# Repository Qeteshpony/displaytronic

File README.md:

# Displaytronic VS2812 Driver Board

Replacement driver board and firmware for the Displaytronic VS2812 flipdot display (28×12 dots).

> **Status:** Work in progress – hardware not yet built or tested.

## Contents

| Path | Description |
|---|---|
| [`pcb/`](pcb/) | KiCad project of the driver board – see [Hardware Documentation](https://qeteshpony.github.io/displaytronic) |
| [`firmware/`](firmware/) | ATmega328P firmware (PlatformIO) – see [firmware README](firmware/README.md) |
| [`flipdot board/`](flipdot%20board/) | Reverse engineered schematics of the display itself |

Prebuilt firmware and production files are attached to each [release](https://github.com/Qeteshpony/displaytronic/releases). Changes are listed in the [changelog](CHANGELOG.md).

## License

- Hardware: [CERN-OHL-P-2.0](LICENSE-CERN-OHL-P-2.0)
- Firmware: [BSD-2-Clause](LICENSE-BSD-2-Clause)

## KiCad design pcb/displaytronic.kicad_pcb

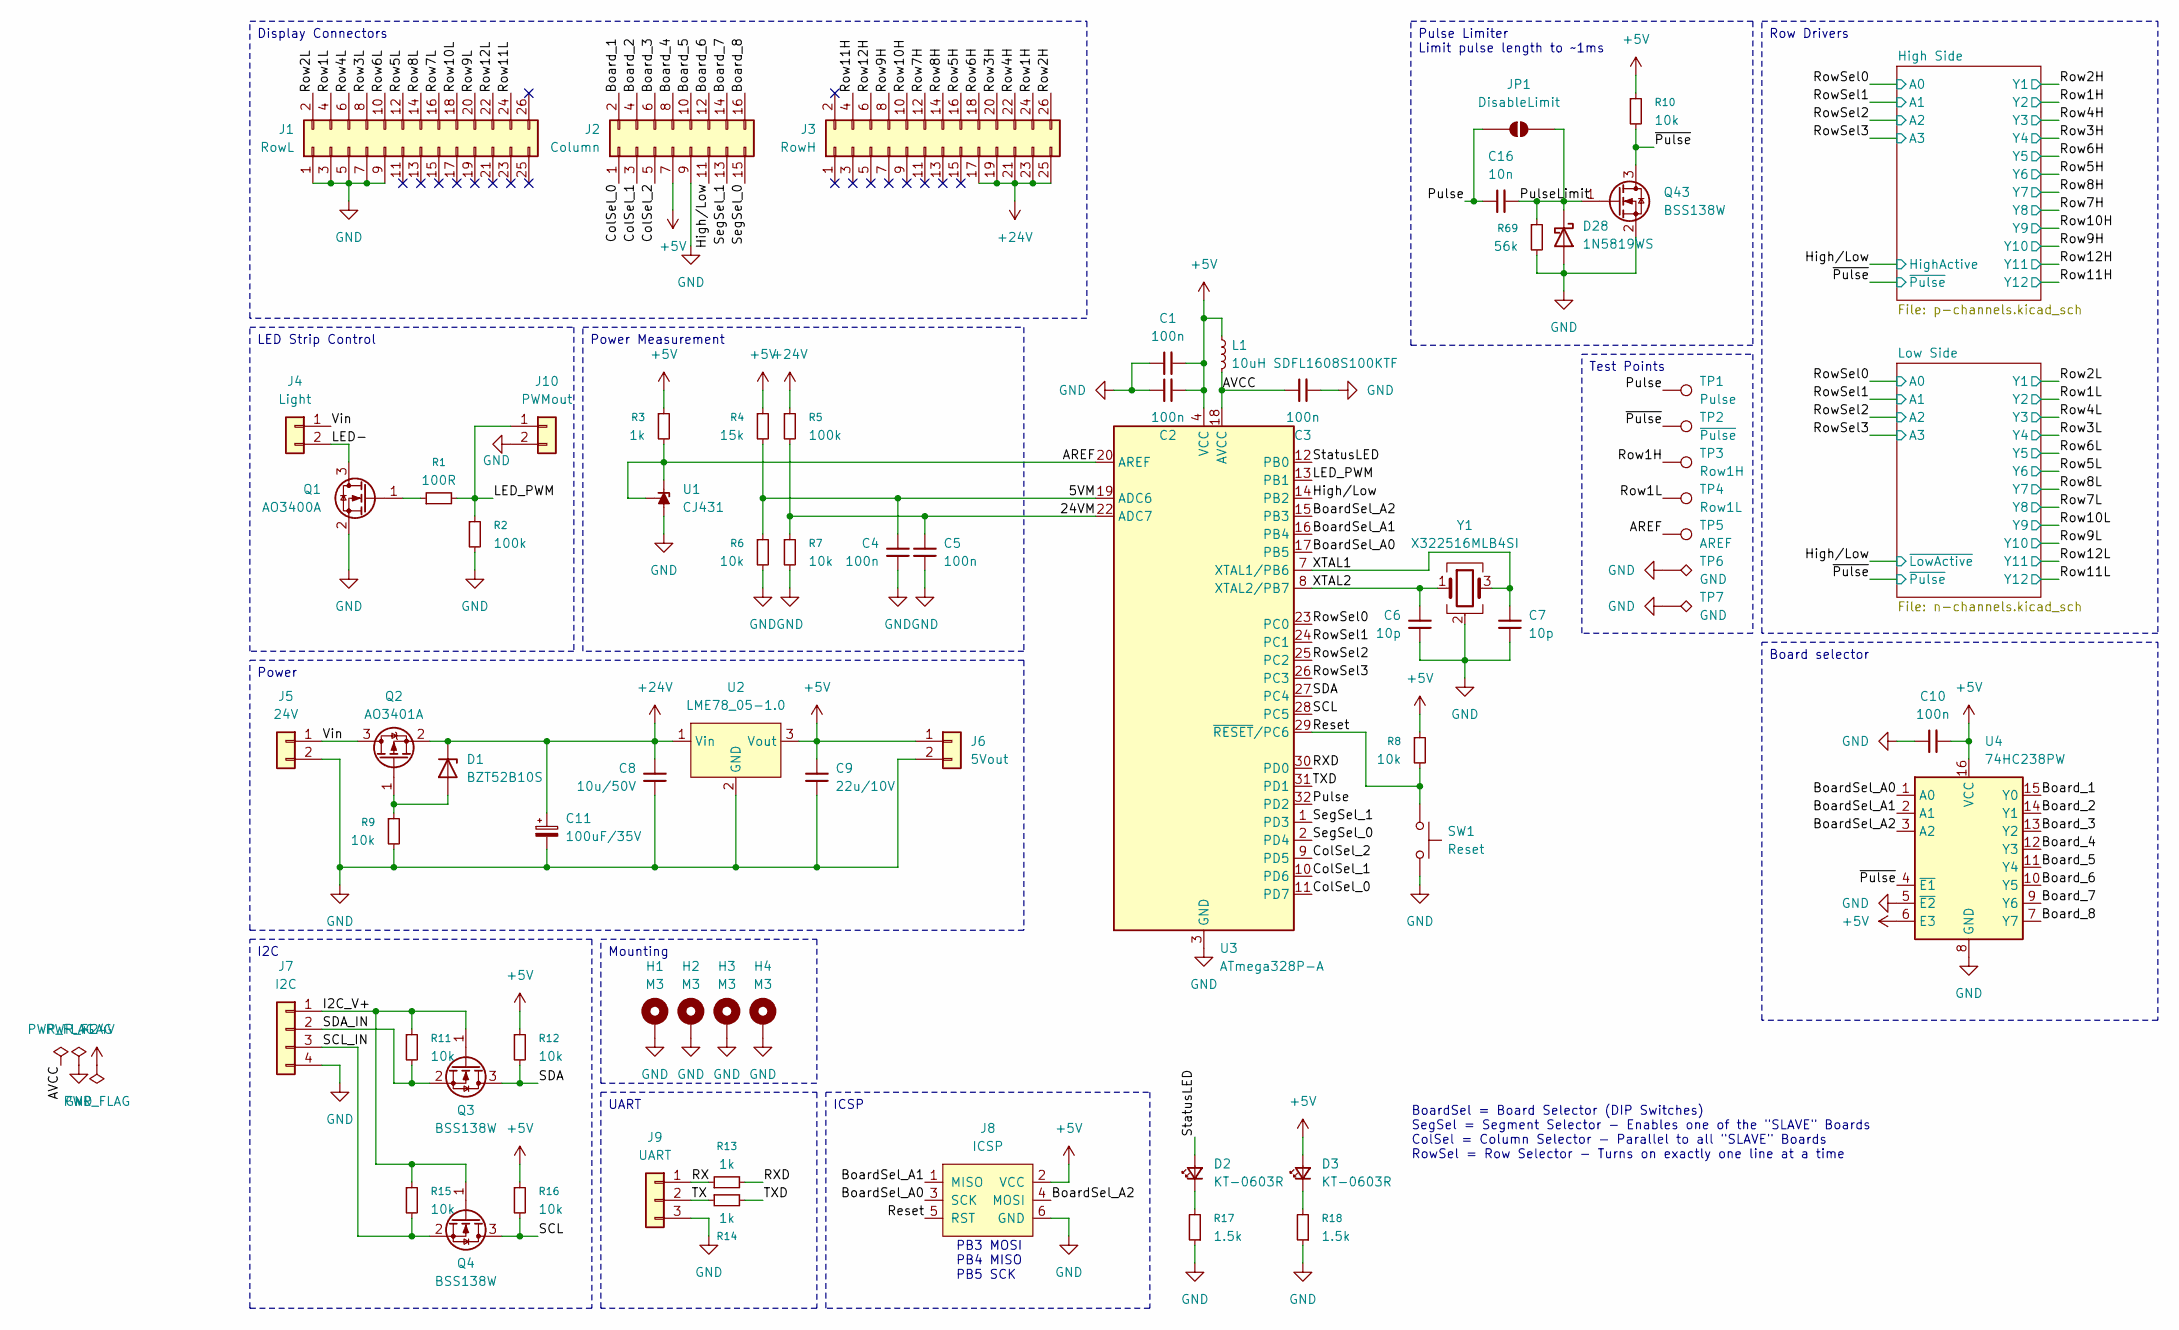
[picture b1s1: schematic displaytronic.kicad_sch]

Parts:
C1, C2, C3, C4, C5, C10: 100n; C_0402_1005Metric; LCSC C307331
C6, C7: 10p; C_0402_1005Metric; LCSC C32949
C8: 10u/50V; C_1206_3216Metric; LCSC C13585
C9: 22u/10V; C_1206_3216Metric; LCSC C12891
C11: 100uF/35V; CP_Radial_D8.0mm_P3.50mm
C16: 10n; C_0402_1005Metric; LCSC C15195
D1: BZT52B10S; D_SOD-323; LCSC C22399886
D2, D3: KT-0603R; LED_0603_1608Metric; LCSC C2286
D28: 1N5819WS; D_SOD-323; LCSC C191023
H1, H2, H3, H4: M3; MountingHole_3.2mm_M3_Pad
J1: RowL; IDC-Header_2x13_P2.54mm_Vertical
J2: Column; IDC-Header_2x08_P2.54mm_Vertical
J3: RowH; IDC-Header_2x13_P2.54mm_Vertical
J4: Light; CTB9352-2
J5: 24V; CTB9352-2
J6: 5Vout; JST_PH_B2B-PH-K_1x02_P2.00mm_Vertical
J7: I2C; JST_PH_B4B-PH-K_1x04_P2.00mm_Vertical
J8: ICSP; PinHeader_2x03_P2.54mm_Vertical
J9: UART; JST_PH_B3B-PH-K_1x03_P2.00mm_Vertical
J10: PWMout; JST_PH_B2B-PH-K_1x02_P2.00mm_Vertical
JP1: DisableLimit; SolderJumper-2_P1.3mm_Open_RoundedPad1.0x1.5mm
L1: 10uH SDFL1608S100KTF; L_0603_1608Metric; LCSC C1035
Q1: AO3400A; SOT-23; LCSC C20917
Q2: AO3401A; SOT-23; LCSC C15127
Q3, Q4, Q43: BSS138W; SOT-323_SC-70; LCSC C28646265
R1: 100R; R_0402_1005Metric; LCSC C25076
R2, R5: 100k; R_0402_1005Metric; LCSC C25741
R3, R13, R14: 1k; R_0402_1005Metric; LCSC C11702
R4: 15k; R_0402_1005Metric; LCSC C25756
R6, R7, R8, R9, R10, R11, R12, R15, R16: 10k; R_0402_1005Metric; LCSC C25744
R17, R18: 1.5k; R_0402_1005Metric; LCSC C25867
R69: 56k; R_0402_1005Metric; LCSC C25796
SW1: Reset; SW_Push_SPST_NO_Alps_SKRK; LCSC C720477
TP1: Pulse; TestPoint_Pad_D2.0mm
TP2: ~{Pulse}; TestPoint_Pad_D2.0mm
TP3: Row1H; TestPoint_Pad_D2.0mm
TP4: Row1L; TestPoint_Pad_D2.0mm
TP5: AREF; TestPoint_Pad_D2.0mm
TP6, TP7: GND; TestPoint_Pad_2.0x2.0mm
U1: CJ431; SOT-23; LCSC C3113
U2: LME78_05-1.0; LME78_1.0-Series
U3: ATmega328P-A; TQFP-32_7x7mm_P0.8mm; LCSC C14877
U4: 74HC238PW; TSSOP-16_4.4x5mm_P0.65mm; LCSC C60434
Y1: X322516MLB4SI; Crystal_SMD_3225-4Pin_3.2x2.5mm; LCSC C13738

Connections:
+5V: C1.2, C2.2, C9.2, C10.2, D3.2 (A), J2.7, J6.1, J8.2 (VCC), L1.1, R3.1, R4.1, R8.1, R10.1, R12.1, R16.1, U2.3 (Vout), U3.4 (VCC), U3.6 (VCC), U4.6 (E3), U4.16 (VCC); also elsewhere on the board
+24V: C8.2, C11.1, D1.1 (K), J3.17, J3.19, J3.21, J3.23, J3.25, Q2.2 (S), R5.1, U2.1 (Vin); also elsewhere on the board
/5VM: C4.2, R4.2, R6.1, U3.19 (ADC6)
/24VM: C5.2, R5.2, R7.1, U3.22 (ADC7)
/AREF: R3.2, TP5.1 (1_1), U1.1 (K), U1.2 (REF), U3.20 (AREF)
/AVCC: C3.2, L1.2, U3.18 (AVCC)
/BoardSel_A0: J8.3 (SCK), U3.17 (PB5), U4.1 (A0)
/BoardSel_A1: J8.1 (MISO), U3.16 (PB4), U4.2 (A1)
/BoardSel_A2: J8.4 (MOSI), U3.15 (PB3), U4.3 (A2)
/Board_1: J2.2, U4.15 (Y0)
/Board_2: J2.4, U4.14 (Y1)
/Board_3: J2.6, U4.13 (Y2)
/Board_4: J2.8, U4.12 (Y3)
/Board_5: J2.10, U4.11 (Y4)
/Board_6: J2.12, U4.10 (Y5)
/Board_7: J2.14, U4.9 (Y6)
/Board_8: J2.16, U4.7 (Y7)
/ColSel_0: J2.1, U3.11 (PD7)
/ColSel_1: J2.3, U3.10 (PD6)
/ColSel_2: J2.5, U3.9 (PD5)
/High/Low: J2.11, U3.14 (PB2); also elsewhere on the board
/I2C_V+: J7.1, Q3.1 (G), Q4.1 (G), R11.1, R15.1
/LED-: J4.2, Q1.3 (D)
/LED_PWM: J10.1, R1.2, R2.1, U3.13 (PB1)
/Pulse: C16.2, JP1.1 (A), TP1.1 (1_1), U3.32 (PD2)
/PulseLimit: C16.1, D28.1 (K), JP1.2 (B), Q43.1 (G), R69.1
/RX: J9.1, R13.1
/RXD: R13.2, U3.30 (PD0)
/Reset: J8.5 (RST), R8.2, SW1.1, U3.29 (~RESET/PC6)
/Row1H: J3.24, TP3.1 (1_1); also elsewhere on the board
/Row1L: J1.4, TP4.1 (1_1); also elsewhere on the board
/Row2H: J3.26; also elsewhere on the board
/Row2L: J1.2; also elsewhere on the board
/Row3H: J3.20; also elsewhere on the board
/Row3L: J1.8; also elsewhere on the board
/Row4H: J3.22; also elsewhere on the board
/Row4L: J1.6; also elsewhere on the board
/Row5H: J3.16; also elsewhere on the board
/Row5L: J1.12; also elsewhere on the board
/Row6H: J3.18; also elsewhere on the board
/Row6L: J1.10; also elsewhere on the board
/Row7H: J3.12; also elsewhere on the board
/Row7L: J1.16; also elsewhere on the board
/Row8H: J3.14; also elsewhere on the board
/Row8L: J1.14; also elsewhere on the board
/Row9H: J3.8; also elsewhere on the board
/Row9L: J1.20; also elsewhere on the board
/Row10H: J3.10; also elsewhere on the board
/Row10L: J1.18; also elsewhere on the board
/Row11H: J3.4; also elsewhere on the board
/Row11L: J1.24; also elsewhere on the board
/Row12H: J3.6; also elsewhere on the board
/Row12L: J1.22; also elsewhere on the board
/RowSel0: U3.23 (PC0); also elsewhere on the board
/RowSel1: U3.24 (PC1); also elsewhere on the board
/RowSel2: U3.25 (PC2); also elsewhere on the board
/RowSel3: U3.26 (PC3); also elsewhere on the board
/SCL: Q4.3 (D), R16.2, U3.28 (PC5)
/SCL_IN: J7.3, Q4.2 (S), R15.2
/SDA: Q3.3 (D), R12.2, U3.27 (PC4)
/SDA_IN: J7.2, Q3.2 (S), R11.2
/SegSel_0: J2.15, U3.2 (PD4)
/SegSel_1: J2.13, U3.1 (PD3)
/StatusLED: D2.2 (A), U3.12 (PB0)
/TX: J9.2, R14.1
/TXD: R14.2, U3.31 (PD1)
/Vin: J4.1, J5.1, Q2.3 (D)
/XTAL1: C7.2, U3.7 (XTAL1/PB6), Y1.3
/XTAL2: C6.2, U3.8 (XTAL2/PB7), Y1.1
/~Pulse: Q43.3 (D), R10.2, TP2.1 (1_1), U4.4 (~E1); also elsewhere on the board
GND: C1.1, C2.1, C3.1, C4.1, C5.1, C6.1, C7.1, C8.1, C9.1, C10.1, C11.2, D28.2 (A), H1.1 (1_1), H2.1 (1_1), H3.1 (1_1), H4.1 (1_1), J1.1, J1.3, J1.5, J1.7, J1.9, J2.9, J5.2, J6.2, J7.4, J8.6 (GND), J9.3, J10.2, Q1.2 (S), Q43.2 (S), R2.2, R6.2, R7.2, R9.2, R17.1, R18.1, R69.2, SW1.2, TP6.1 (1_1), TP7.1 (1_1), U1.3 (A), U2.2 (GND), U3.3 (GND), U3.5 (GND), U3.21 (GND), U4.5 (~E2), U4.8 (GND), Y1.2 (G), Y1.4 (G); also elsewhere on the board
unnamed: D1.2 (A), Q2.1 (G), R9.1
unnamed: D2.1 (K), R17.2
unnamed: D3.1 (K), R18.2
unnamed: Q1.1 (G), R1.1

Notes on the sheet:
PB3 MOSI PB4 MISO PB5 SCK
BoardSel = Board Selector (DIP Switches) SegSel = Segment Selector - Enables one of the "SLAVE" Boards ColSel = Column Selector - Parallel to all "SLAVE" Boards RowSel = Row Selector - Turns on exactly one line at a time
Mounting
Board selector
ICSP
UART
Power Measurement
LED Strip Control
I2C
Pulse Limiter Limit pulse length to ~1ms
Row Drivers
Power
Test Points
Display Connectors

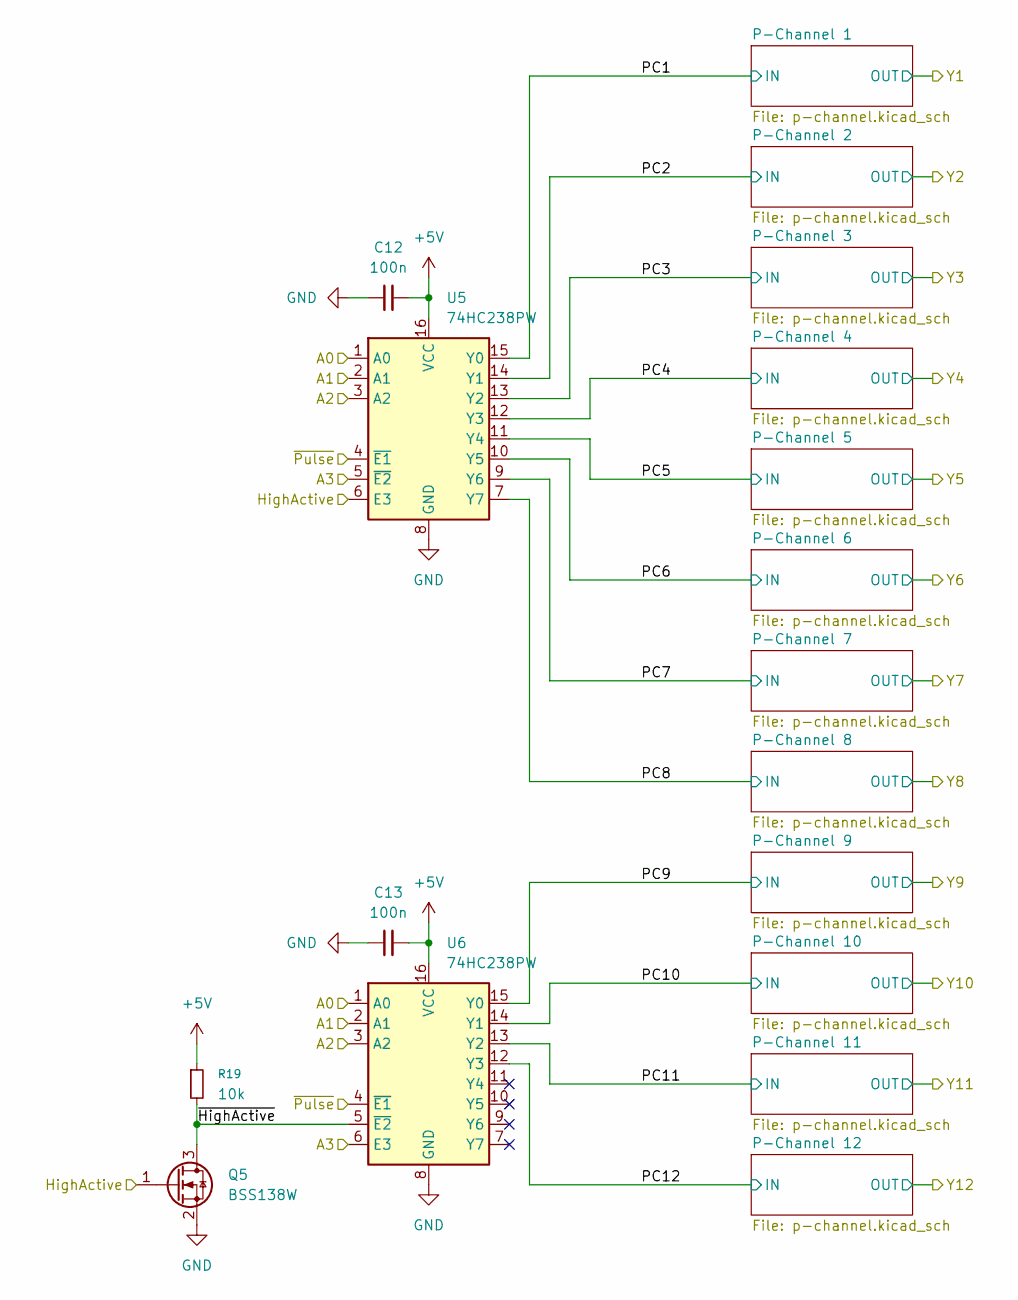
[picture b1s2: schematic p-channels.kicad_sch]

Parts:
C12, C13: 100n; C_0402_1005Metric; LCSC C307331
Q5: BSS138W; SOT-323_SC-70; LCSC C28646265
R19: 10k; R_0402_1005Metric; LCSC C25744
U5, U6: 74HC238PW; TSSOP-16_4.4x5mm_P0.65mm; LCSC C60434

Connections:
+5V: C12.2, C13.2, R19.1, U5.16 (VCC), U6.16 (VCC); also elsewhere on the board
/High Side/PC1: U5.15 (Y0); also elsewhere on the board
/High Side/PC2: U5.14 (Y1); also elsewhere on the board
/High Side/PC3: U5.13 (Y2); also elsewhere on the board
/High Side/PC4: U5.12 (Y3); also elsewhere on the board
/High Side/PC5: U5.11 (Y4); also elsewhere on the board
/High Side/PC6: U5.10 (Y5); also elsewhere on the board
/High Side/PC7: U5.9 (Y6); also elsewhere on the board
/High Side/PC8: U5.7 (Y7); also elsewhere on the board
/High Side/PC9: U6.15 (Y0); also elsewhere on the board
/High Side/PC10: U6.14 (Y1); also elsewhere on the board
/High Side/PC11: U6.13 (Y2); also elsewhere on the board
/High Side/PC12: U6.12 (Y3); also elsewhere on the board
/High Side/~HighActive: Q5.3 (D), R19.2, U6.5 (~E2)
/High/Low: Q5.1 (G), U5.6 (E3); also elsewhere on the board
/RowSel0: U5.1 (A0), U6.1 (A0); also elsewhere on the board
/RowSel1: U5.2 (A1), U6.2 (A1); also elsewhere on the board
/RowSel2: U5.3 (A2), U6.3 (A2); also elsewhere on the board
/RowSel3: U5.5 (~E2), U6.6 (E3); also elsewhere on the board
/~Pulse: U5.4 (~E1), U6.4 (~E1); also elsewhere on the board
GND: C12.1, C13.1, Q5.2 (S), U5.8 (GND), U6.8 (GND); also elsewhere on the board

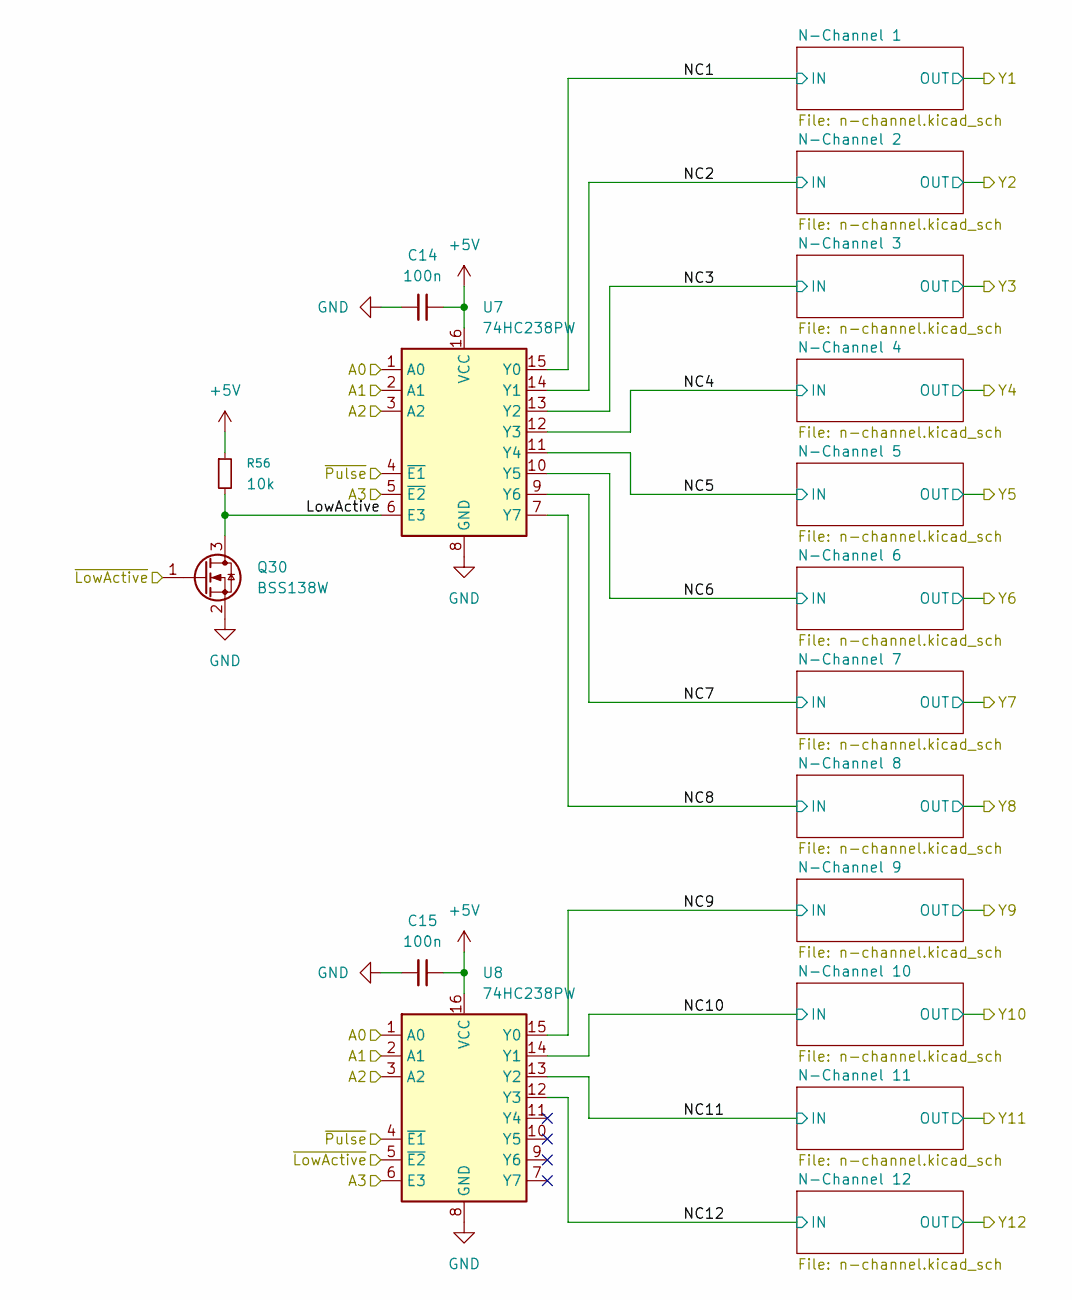
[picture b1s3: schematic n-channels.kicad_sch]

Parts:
C14, C15: 100n; C_0402_1005Metric; LCSC C307331
Q30: BSS138W; SOT-323_SC-70; LCSC C28646265
R56: 10k; R_0402_1005Metric; LCSC C25744
U7, U8: 74HC238PW; TSSOP-16_4.4x5mm_P0.65mm; LCSC C60434

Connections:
+5V: C14.2, C15.2, R56.1, U7.16 (VCC), U8.16 (VCC); also elsewhere on the board
/High/Low: Q30.1 (G), U8.5 (~E2); also elsewhere on the board
/Low Side/LowActive: Q30.3 (D), R56.2, U7.6 (E3)
/Low Side/NC1: U7.15 (Y0); also elsewhere on the board
/Low Side/NC2: U7.14 (Y1); also elsewhere on the board
/Low Side/NC3: U7.13 (Y2); also elsewhere on the board
/Low Side/NC4: U7.12 (Y3); also elsewhere on the board
/Low Side/NC5: U7.11 (Y4); also elsewhere on the board
/Low Side/NC6: U7.10 (Y5); also elsewhere on the board
/Low Side/NC7: U7.9 (Y6); also elsewhere on the board
/Low Side/NC8: U7.7 (Y7); also elsewhere on the board
/Low Side/NC9: U8.15 (Y0); also elsewhere on the board
/Low Side/NC10: U8.14 (Y1); also elsewhere on the board
/Low Side/NC11: U8.13 (Y2); also elsewhere on the board
/Low Side/NC12: U8.12 (Y3); also elsewhere on the board
/RowSel0: U7.1 (A0), U8.1 (A0); also elsewhere on the board
/RowSel1: U7.2 (A1), U8.2 (A1); also elsewhere on the board
/RowSel2: U7.3 (A2), U8.3 (A2); also elsewhere on the board
/RowSel3: U7.5 (~E2), U8.6 (E3); also elsewhere on the board
/~Pulse: U7.4 (~E1), U8.4 (~E1); also elsewhere on the board
GND: C14.1, C15.1, Q30.2 (S), U7.8 (GND), U8.8 (GND); also elsewhere on the board

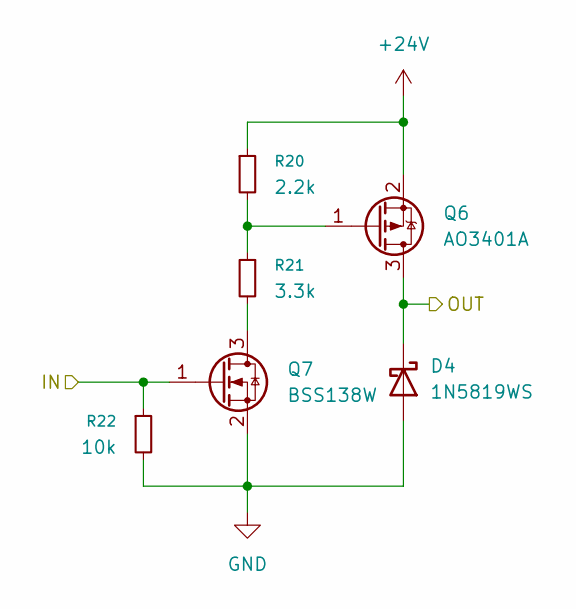
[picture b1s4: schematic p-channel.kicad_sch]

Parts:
D4: 1N5819WS; D_SOD-323; LCSC C191023
Q6: AO3401A; SOT-23; LCSC C15127
Q7: BSS138W; SOT-323_SC-70; LCSC C28646265
R20: 2.2k; R_0402_1005Metric; LCSC C25879
R21: 3.3k; R_0402_1005Metric; LCSC C25890
R22: 10k; R_0402_1005Metric; LCSC C25744

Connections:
+24V: Q6.2 (S), R20.1; also elsewhere on the board
/High Side/PC1: Q7.1 (G), R22.1; also elsewhere on the board
/Row2H: D4.1 (K), Q6.3 (D); also elsewhere on the board
GND: D4.2 (A), Q7.2 (S), R22.2; also elsewhere on the board
unnamed: Q6.1 (G), R20.2, R21.1
unnamed: Q7.3 (D), R21.2

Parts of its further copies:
D5, D6, D7, D8, D9, D10, D11, D12, D13, D14, D15: 1N5819WS; D_SOD-323; LCSC C191023
Q8, Q10, Q12, Q14, Q16, Q18, Q20, Q22, Q24, Q26, Q28: AO3401A; SOT-23; LCSC C15127
Q9, Q11, Q13, Q15, Q17, Q19, Q21, Q23, Q25, Q27, Q29: BSS138W; SOT-323_SC-70; LCSC C28646265
R23, R26, R29, R32, R35, R38, R41, R44, R47, R50, R53: 2.2k; R_0402_1005Metric; LCSC C25879
R24, R27, R30, R33, R36, R39, R42, R45, R48, R51, R54: 3.3k; R_0402_1005Metric; LCSC C25890
R25, R28, R31, R34, R37, R40, R43, R46, R49, R52, R55: 10k; R_0402_1005Metric; LCSC C25744

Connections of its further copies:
+24V: Q8.2 (S), Q10.2 (S), Q12.2 (S), Q14.2 (S), Q16.2 (S), Q18.2 (S), Q20.2 (S), Q22.2 (S), Q24.2 (S), Q26.2 (S), Q28.2 (S), R23.1, R26.1, R29.1, R32.1, R35.1, R38.1, R41.1, R44.1, R47.1, R50.1, R53.1; also elsewhere on the board
/High Side/PC2: Q9.1 (G), R25.1; also elsewhere on the board
/High Side/PC3: Q11.1 (G), R28.1; also elsewhere on the board
/High Side/PC4: Q13.1 (G), R31.1; also elsewhere on the board
/High Side/PC5: Q15.1 (G), R34.1; also elsewhere on the board
/High Side/PC6: Q17.1 (G), R37.1; also elsewhere on the board
/High Side/PC7: Q19.1 (G), R40.1; also elsewhere on the board
/High Side/PC8: Q21.1 (G), R43.1; also elsewhere on the board
/High Side/PC9: Q23.1 (G), R46.1; also elsewhere on the board
/High Side/PC10: Q25.1 (G), R49.1; also elsewhere on the board
/High Side/PC11: Q27.1 (G), R52.1; also elsewhere on the board
/High Side/PC12: Q29.1 (G), R55.1; also elsewhere on the board
/Row1H: D5.1 (K), Q8.3 (D); also elsewhere on the board
/Row3H: D7.1 (K), Q12.3 (D); also elsewhere on the board
/Row4H: D6.1 (K), Q10.3 (D); also elsewhere on the board
/Row5H: D9.1 (K), Q16.3 (D); also elsewhere on the board
/Row6H: D8.1 (K), Q14.3 (D); also elsewhere on the board
/Row7H: D11.1 (K), Q20.3 (D); also elsewhere on the board
/Row8H: D10.1 (K), Q18.3 (D); also elsewhere on the board
/Row9H: D13.1 (K), Q24.3 (D); also elsewhere on the board
/Row10H: D12.1 (K), Q22.3 (D); also elsewhere on the board
/Row11H: D15.1 (K), Q28.3 (D); also elsewhere on the board
/Row12H: D14.1 (K), Q26.3 (D); also elsewhere on the board
GND: D5.2 (A), D6.2 (A), D7.2 (A), D8.2 (A), D9.2 (A), D10.2 (A), D11.2 (A), D12.2 (A), D13.2 (A), D14.2 (A), D15.2 (A), Q9.2 (S), Q11.2 (S), Q13.2 (S), Q15.2 (S), Q17.2 (S), Q19.2 (S), Q21.2 (S), Q23.2 (S), Q25.2 (S), Q27.2 (S), Q29.2 (S), R25.2, R28.2, R31.2, R34.2, R37.2, R40.2, R43.2, R46.2, R49.2, R52.2, R55.2; also elsewhere on the board
unnamed: Q8.1 (G), R23.2, R24.1
unnamed: Q9.3 (D), R24.2
unnamed: Q10.1 (G), R26.2, R27.1
unnamed: Q11.3 (D), R27.2
unnamed: Q12.1 (G), R29.2, R30.1
unnamed: Q13.3 (D), R30.2
unnamed: Q14.1 (G), R32.2, R33.1
unnamed: Q15.3 (D), R33.2
unnamed: Q16.1 (G), R35.2, R36.1
unnamed: Q17.3 (D), R36.2
unnamed: Q18.1 (G), R38.2, R39.1
unnamed: Q19.3 (D), R39.2
unnamed: Q20.1 (G), R41.2, R42.1
unnamed: Q21.3 (D), R42.2
unnamed: Q22.1 (G), R44.2, R45.1
unnamed: Q23.3 (D), R45.2
unnamed: Q24.1 (G), R47.2, R48.1
unnamed: Q25.3 (D), R48.2
unnamed: Q26.1 (G), R50.2, R51.1
unnamed: Q27.3 (D), R51.2
unnamed: Q28.1 (G), R53.2, R54.1
unnamed: Q29.3 (D), R54.2

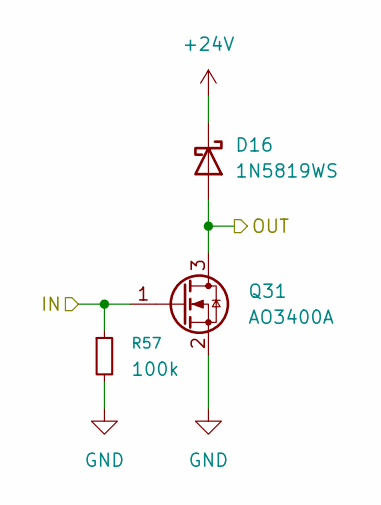
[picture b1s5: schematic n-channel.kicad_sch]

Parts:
D16: 1N5819WS; D_SOD-323; LCSC C191023
Q31: AO3400A; SOT-23; LCSC C20917
R57: 100k; R_0402_1005Metric; LCSC C25741

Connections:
+24V: D16.1 (K); also elsewhere on the board
/Low Side/NC1: Q31.1 (G), R57.1; also elsewhere on the board
/Row2L: D16.2 (A), Q31.3 (D); also elsewhere on the board
GND: Q31.2 (S), R57.2; also elsewhere on the board

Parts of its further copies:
D17, D18, D19, D20, D21, D22, D23, D24, D25, D26, D27: 1N5819WS; D_SOD-323; LCSC C191023
Q32, Q33, Q34, Q35, Q36, Q37, Q38, Q39, Q40, Q41, Q42: AO3400A; SOT-23; LCSC C20917
R58, R59, R60, R61, R62, R63, R64, R65, R66, R67, R68: 100k; R_0402_1005Metric; LCSC C25741

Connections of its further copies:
+24V: D17.1 (K), D18.1 (K), D19.1 (K), D20.1 (K), D21.1 (K), D22.1 (K), D23.1 (K), D24.1 (K), D25.1 (K), D26.1 (K), D27.1 (K); also elsewhere on the board
/Low Side/NC2: Q32.1 (G), R58.1; also elsewhere on the board
/Low Side/NC3: Q33.1 (G), R59.1; also elsewhere on the board
/Low Side/NC4: Q34.1 (G), R60.1; also elsewhere on the board
/Low Side/NC5: Q35.1 (G), R61.1; also elsewhere on the board
/Low Side/NC6: Q36.1 (G), R62.1; also elsewhere on the board
/Low Side/NC7: Q37.1 (G), R63.1; also elsewhere on the board
/Low Side/NC8: Q38.1 (G), R64.1; also elsewhere on the board
/Low Side/NC9: Q39.1 (G), R65.1; also elsewhere on the board
/Low Side/NC10: Q40.1 (G), R66.1; also elsewhere on the board
/Low Side/NC11: Q41.1 (G), R67.1; also elsewhere on the board
/Low Side/NC12: Q42.1 (G), R68.1; also elsewhere on the board
/Row1L: D17.2 (A), Q32.3 (D); also elsewhere on the board
/Row3L: D19.2 (A), Q34.3 (D); also elsewhere on the board
/Row4L: D18.2 (A), Q33.3 (D); also elsewhere on the board
/Row5L: D21.2 (A), Q36.3 (D); also elsewhere on the board
/Row6L: D20.2 (A), Q35.3 (D); also elsewhere on the board
/Row7L: D23.2 (A), Q38.3 (D); also elsewhere on the board
/Row8L: D22.2 (A), Q37.3 (D); also elsewhere on the board
/Row9L: D25.2 (A), Q40.3 (D); also elsewhere on the board
/Row10L: D24.2 (A), Q39.3 (D); also elsewhere on the board
/Row11L: D27.2 (A), Q42.3 (D); also elsewhere on the board
/Row12L: D26.2 (A), Q41.3 (D); also elsewhere on the board
GND: Q32.2 (S), Q33.2 (S), Q34.2 (S), Q35.2 (S), Q36.2 (S), Q37.2 (S), Q38.2 (S), Q39.2 (S), Q40.2 (S), Q41.2 (S), Q42.2 (S), R58.2, R59.2, R60.2, R61.2, R62.2, R63.2, R64.2, R65.2, R66.2, R67.2, R68.2; also elsewhere on the board

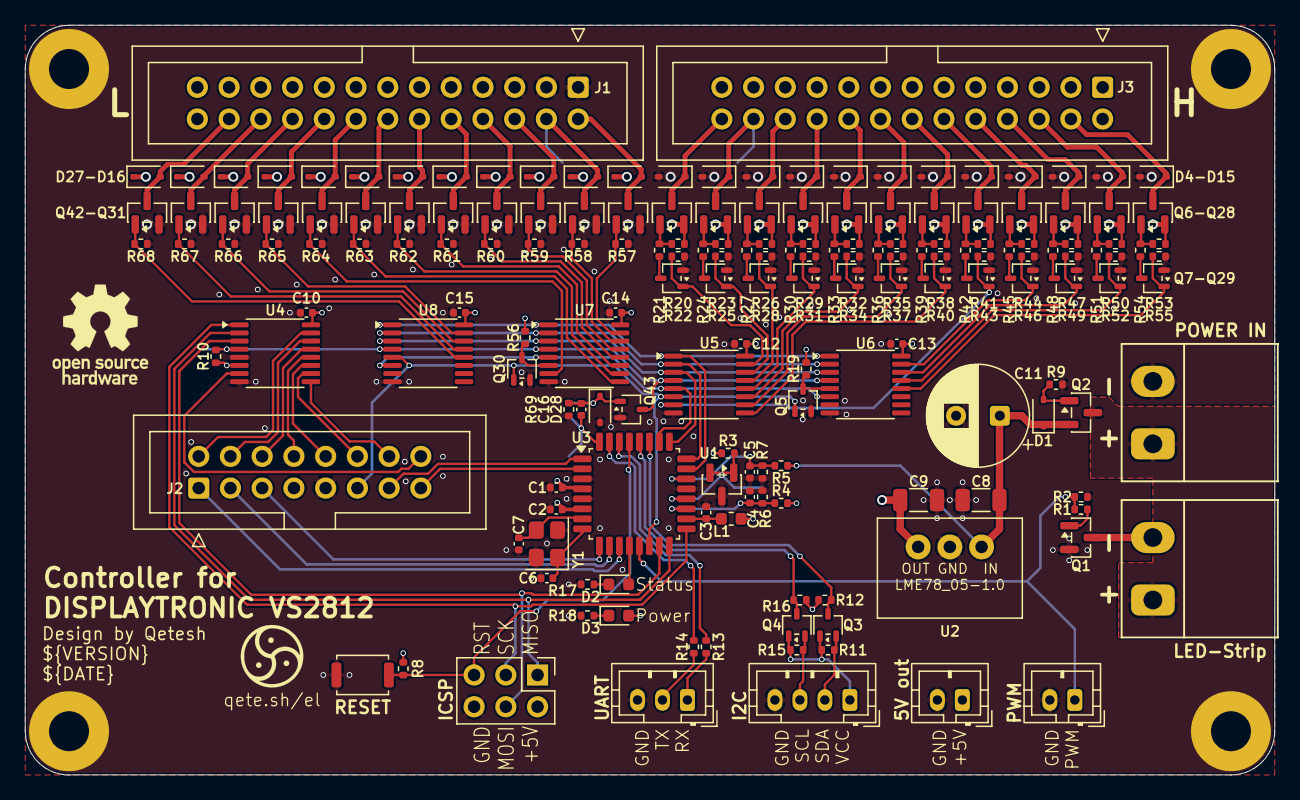
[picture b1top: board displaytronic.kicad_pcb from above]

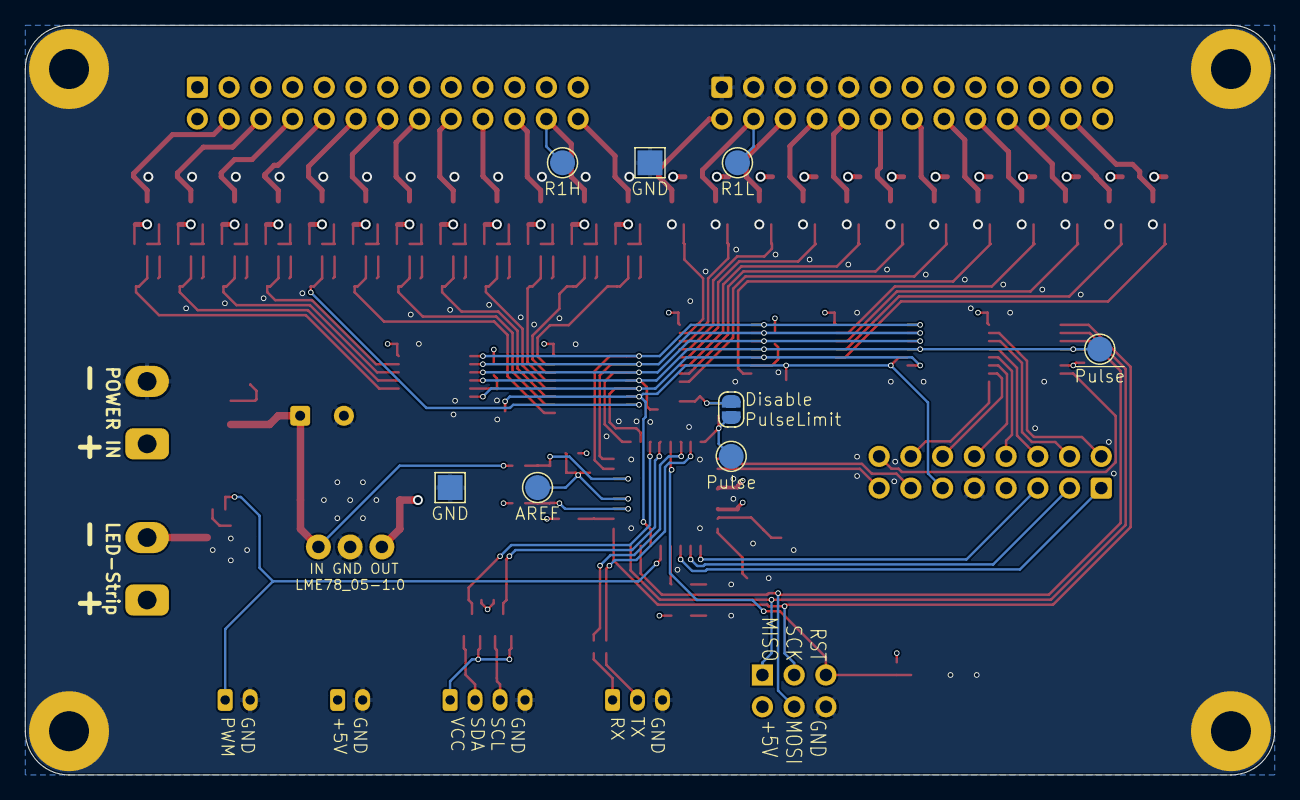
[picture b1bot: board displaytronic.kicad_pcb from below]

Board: 4 copper layers, 100.0 x 60.0 mm, 189 parts (8 on the bottom side), 125 nets.

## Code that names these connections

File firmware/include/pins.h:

// define avr pins

#pragma once
#include <Arduino.h>

// funktion to atmega pin

constexpr uint8_t PIN_STATUS_LED  = PIN_PB0;
constexpr uint8_t PIN_LED_PWM     = PIN_PB1;
constexpr uint8_t PIN_HIGH_LOW    = PIN_PB2;
constexpr uint8_t PIN_BOARDSEL_2 = PIN_PB3;
constexpr uint8_t PIN_BOARDSEL_1 = PIN_PB4;
constexpr uint8_t PIN_BOARDSEL_0 = PIN_PB5;

constexpr uint8_t PIN_ROWSEL_0    = PIN_PC0;
constexpr uint8_t PIN_ROWSEL_1    = PIN_PC1;
constexpr uint8_t PIN_ROWSEL_2    = PIN_PC2;
constexpr uint8_t PIN_ROWSEL_3    = PIN_PC3;
constexpr uint8_t PIN_SDA         = PIN_PC4;
constexpr uint8_t PIN_SCL         = PIN_PC5;

constexpr uint8_t PIN_RXD         = PIN_PD0;
constexpr uint8_t PIN_TXD         = PIN_PD1;
constexpr uint8_t PIN_PULSE       = PIN_PD2;
constexpr uint8_t PIN_SEGSEL_1    = PIN_PD3;
constexpr uint8_t PIN_SEGSEL_0    = PIN_PD4;
constexpr uint8_t PIN_COLSEL_2    = PIN_PD5;
constexpr uint8_t PIN_COLSEL_1    = PIN_PD6;
constexpr uint8_t PIN_COLSEL_0    = PIN_PD7;

constexpr uint8_t PIN_MEASURE_LOGIC = PIN_A6;
constexpr uint8_t PIN_MEASURE_FLIPDOT = PIN_A7;

// pin groups

constexpr uint8_t PINS_BOARD[] = {PIN_BOARDSEL_0, PIN_BOARDSEL_1, PIN_BOARDSEL_2};
constexpr uint8_t PINS_SEGMENT[] = {PIN_SEGSEL_0, PIN_SEGSEL_1};
constexpr uint8_t PINS_COLUMN[] = {PIN_COLSEL_0, PIN_COLSEL_1, PIN_COLSEL_2};
constexpr uint8_t PINS_ROW[] = {PIN_ROWSEL_0, PIN_ROWSEL_1, PIN_ROWSEL_2, PIN_ROWSEL_3};
